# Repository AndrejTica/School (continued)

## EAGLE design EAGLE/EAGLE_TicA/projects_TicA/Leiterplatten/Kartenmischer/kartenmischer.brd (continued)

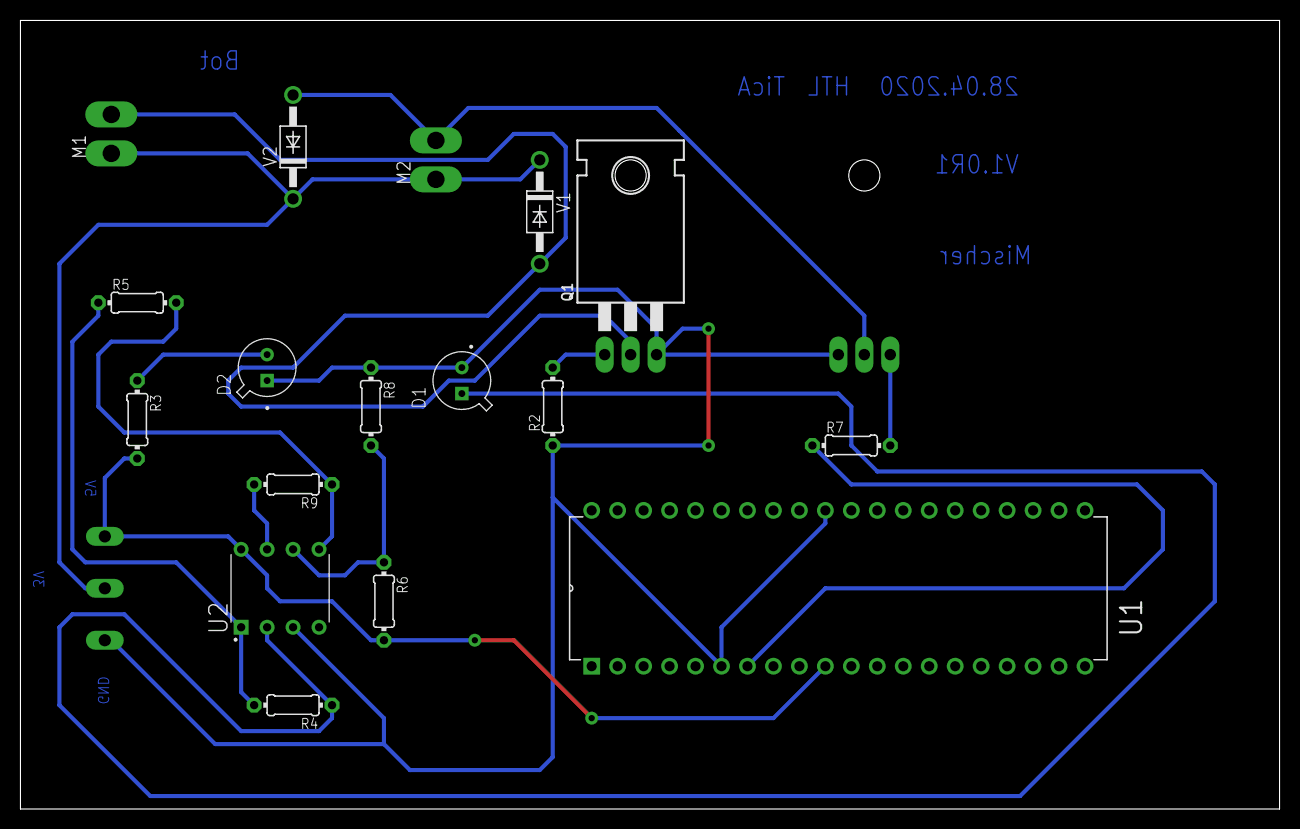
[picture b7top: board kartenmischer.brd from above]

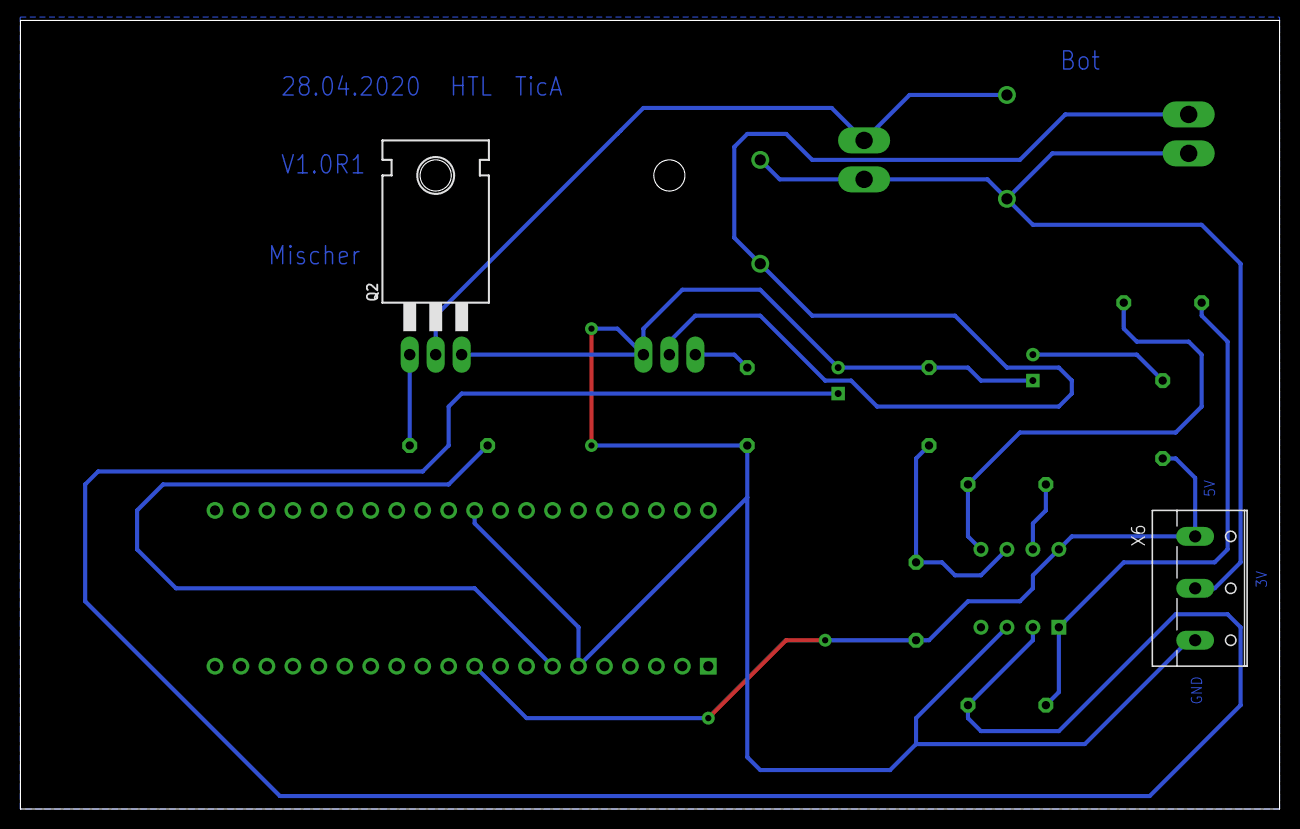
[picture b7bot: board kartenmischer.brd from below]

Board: 2 copper layers, 123.2 x 77.1 mm, 19 parts (2 on the bottom side), 14 nets.

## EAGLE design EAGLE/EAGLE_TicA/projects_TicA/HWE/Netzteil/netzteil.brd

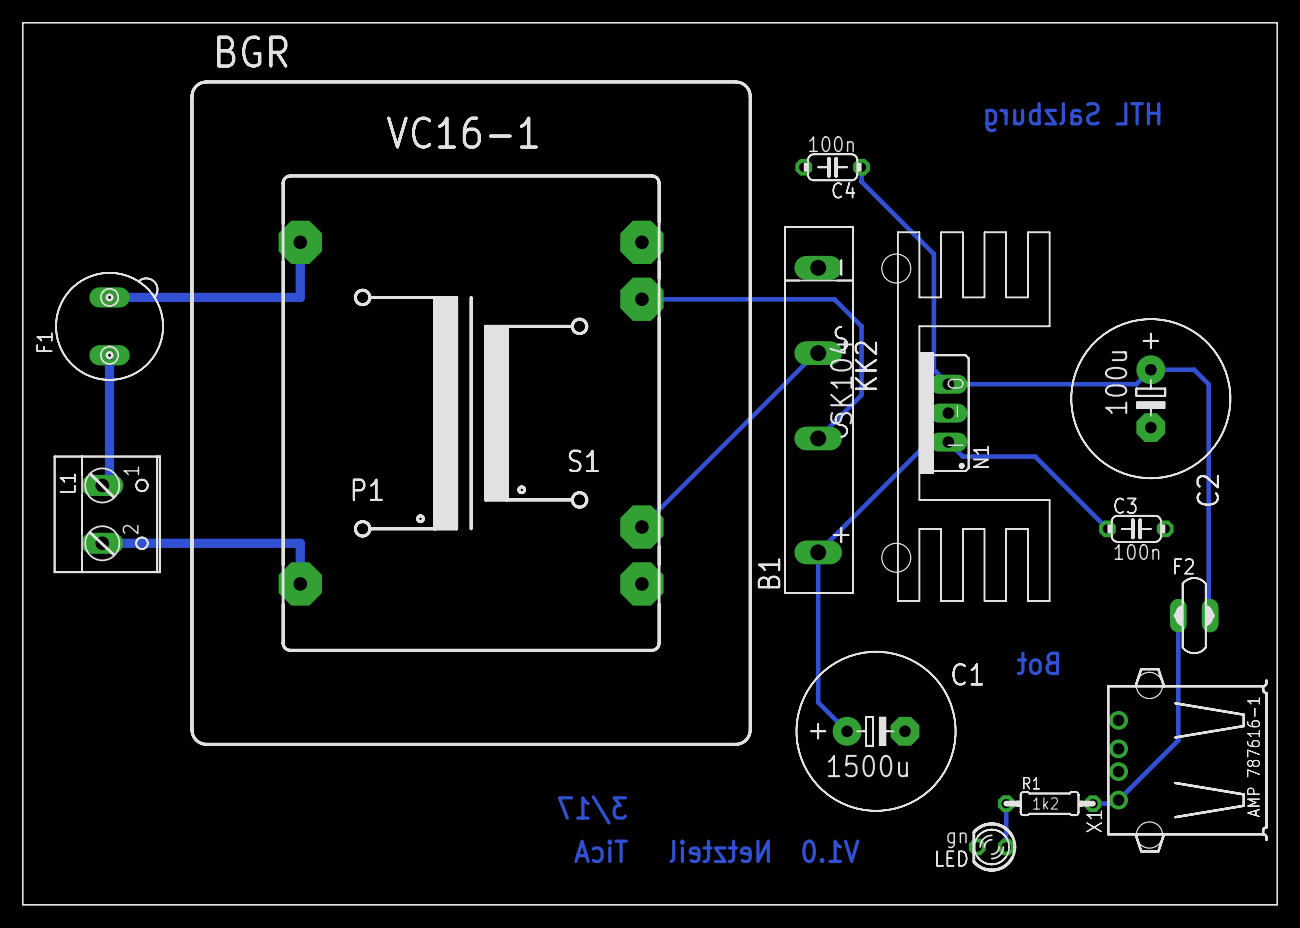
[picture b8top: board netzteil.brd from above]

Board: 2 copper layers, 110.2 x 77.5 mm, 15 parts (0 on the bottom side), 10 nets.

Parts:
B1: FB32
BGR: VC16-1
C1: 1500u; E5-13
C2: 100u; E5-13
C3, C4: 100n; C050-024X044
F1: 19560
F2: P660A
KK2: SK104
L1: W237-132
LED: gn; LED3MM
MEASURE: MEASURE
N1: 78XXS
R1: 1k2; 0204/7
X1: USB

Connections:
GND: B1.-, C1.-, C2.-, C3.2, C4.2, LED.K, N1.GND, X1.4
unnamed: F1.1, L1.1
unnamed: BGR.1, F1.2
unnamed: BGR.7, L1.2
unnamed: B1.AC1, BGR.13
unnamed: B1.AC2, BGR.9
unnamed: F2.1, R1.2, X1.1
unnamed: B1.+, C1.+, C3.1, N1.IN
unnamed: C2.+, C4.1, F2.2, N1.OUT
unnamed: LED.A, R1.1

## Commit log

2020-09-30 FSST Doku
2020-09-30 second commit
2020-09-30 deleted junk file
2020-09-30 changed readme
2020-09-30 Adding DE
2020-09-30 adding AM
2020-09-30 Deleted junk from am
2020-09-30 tidy up of FSST
2020-09-30 bunch of stuff
2020-09-30 new stuff again
2020-09-30 english stuff
2020-10-01 sfsf
2020-10-01 name change
2020-10-02 thicc update
2020-10-02 smoll commit
2020-10-02 clean up
2020-10-03 just triebel things
2020-10-03 dunno
2020-10-05 juicy exams
2020-10-05 1 commit for stoff
2020-10-05 2 commit for stoff
2020-10-05 3 commit for stoff
2020-10-05 4 commit for stoff
2020-10-05 my_linux_script
2020-10-08 new commitele
2020-10-08 new commitele 2
2020-10-08 tests got sorted
2020-10-08 little cleanup
2020-10-08 tests update
2020-10-08 cleanup 1
2020-10-08 Dr. Phil update
2020-10-08 Dr. Phil update the second
2020-10-08 Dr Phil trinity
2020-10-11 linux
2020-10-15 Tests FSST Namen
2020-10-15 Erörterung Schreiben
2020-10-16 Cleanup ksn test
2020-10-16 eagle stuff and mtrs
2020-10-20 fat book
2020-10-20 20.10.2020
2020-10-23 ksn commitele
2020-10-30 printlabor stuff
2020-11-02 new books
2020-11-02 new books 2
2020-11-02 new stuff
2020-11-02 new stuff again 2
2020-11-02 new stuff again 3
2020-11-03 raspberry pi
2020-11-23 myNotesMatura
2020-11-23 test
2020-11-24 exzeß code
2020-11-25 klotz test
2020-11-26 filter
2020-12-14 personal programm
2020-12-15 fsst test
2020-12-15 temp
2020-12-16 english sa
2020-12-19 fsst stuff
2020-12-22 fsst
2020-12-29 new hoffman repo
2021-01-03 3.jan
2021-01-09 Jo wahrscheinlich
2021-01-19 19.1
2021-01-30 company
2021-02-24 dic update
2021-04-28 28.04.2021
